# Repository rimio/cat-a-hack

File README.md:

# cat-a-hack

Prototyping board for PC/μC to ham radio transceiver isolation.

 This work is licensed under a [Creative Commons Attribution-ShareAlike 4.0 International License](http://creativecommons.org/licenses/by-sa/4.0/).

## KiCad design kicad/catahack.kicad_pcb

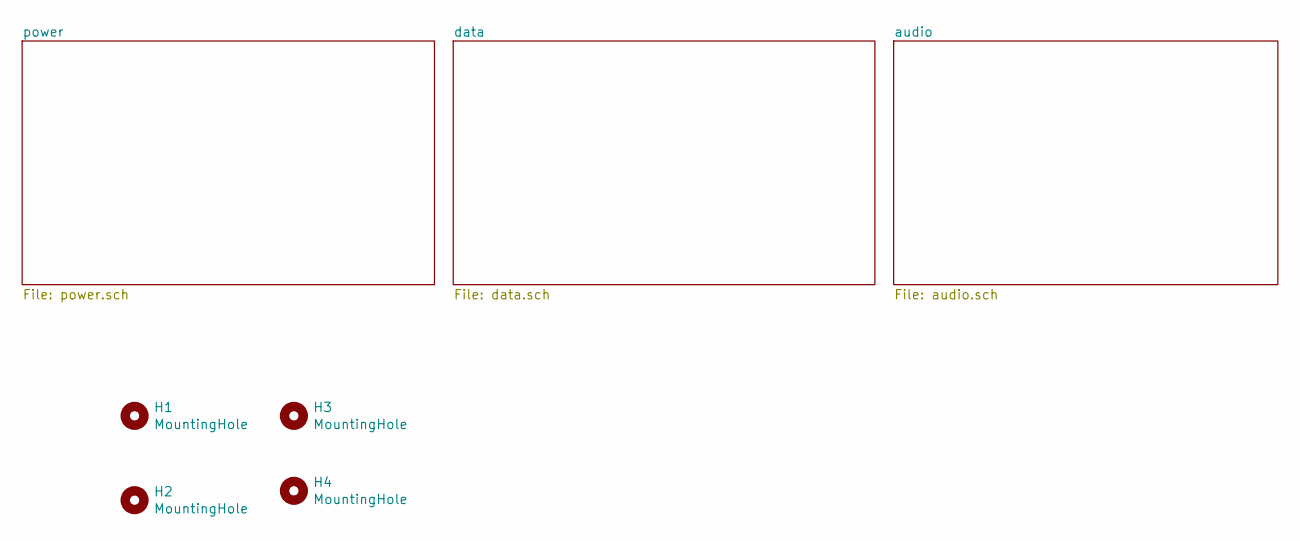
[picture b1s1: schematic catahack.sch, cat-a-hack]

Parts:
H1, H2, H3, H4: MountingHole; MountingHole_4.3mm_M4_ISO7380_Pad

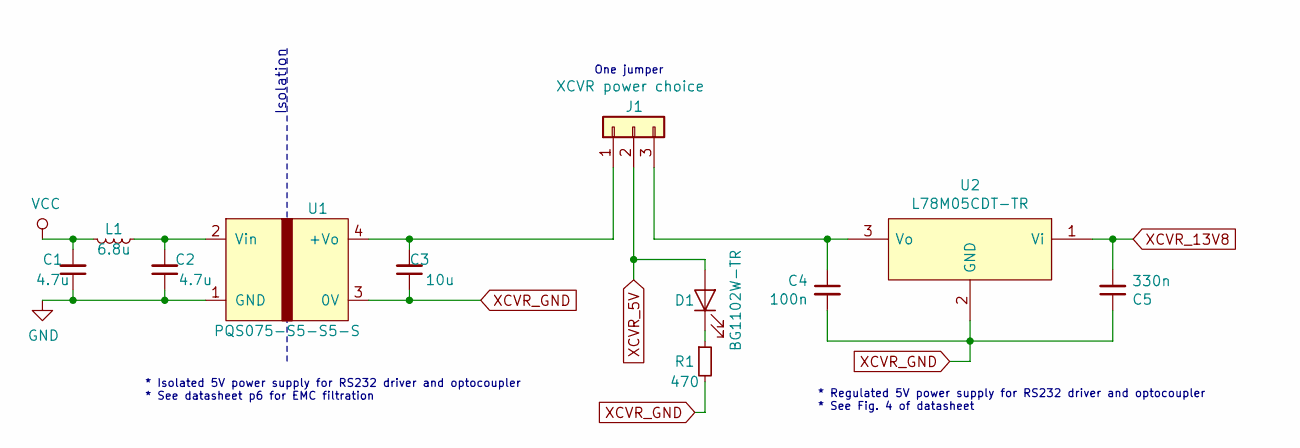
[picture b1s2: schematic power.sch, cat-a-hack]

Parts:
C1, C2: 4.7u; C_1206_3216Metric_Pad1.42x1.75mm_HandSolder
C3: 10u; C_1206_3216Metric_Pad1.42x1.75mm_HandSolder
C4: 100n; C_1206_3216Metric_Pad1.42x1.75mm_HandSolder
C5: 330n; C_1206_3216Metric_Pad1.42x1.75mm_HandSolder
D1: BG1102W-TR; LED_1206_3216Metric_Pad1.42x1.75mm_HandSolder
J1: XCVR power choice; PinHeader_1x03_P2.54mm_Vertical
L1: 6.8u; L_0805_2012Metric_Pad1.15x1.40mm_HandSolder
R1: 470; R_1206_3216Metric_Pad1.42x1.75mm_HandSolder
U1: PQS075-S5-S5-S; SIP-4_PQS075-S5-S5-S
U2: L78M05CDT-TR; TO-252-2; Mouser Part Number 511-L78M05CDT-TR

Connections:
GND: C1.1, C2.1, U1.1 (GND); also elsewhere on the board
unnamed: C2.2, L1.1, U1.2 (Vin)
unnamed: C3.2, J1.1, U1.4 (+Vo)
unnamed: C4.1, J1.3, U2.3 (Vo)
unnamed: D1.1 (K), R1.1
VCC: C1.2, L1.2; also elsewhere on the board
XCVR_5V: D1.2 (A), J1.2; also elsewhere on the board
XCVR_13V8: C5.2, U2.1 (Vi); also elsewhere on the board
XCVR_GND: C3.1, C4.2, C5.1, R1.2, U1.3 (0V), U2.2 (GND); also elsewhere on the board

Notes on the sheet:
* Isolated 5V power supply for RS232 driver and optocoupler * See datasheet p6 for EMC filtration
One jumper
Isolation
* Regulated 5V power supply for RS232 driver and optocoupler * See Fig. 4 of datasheet

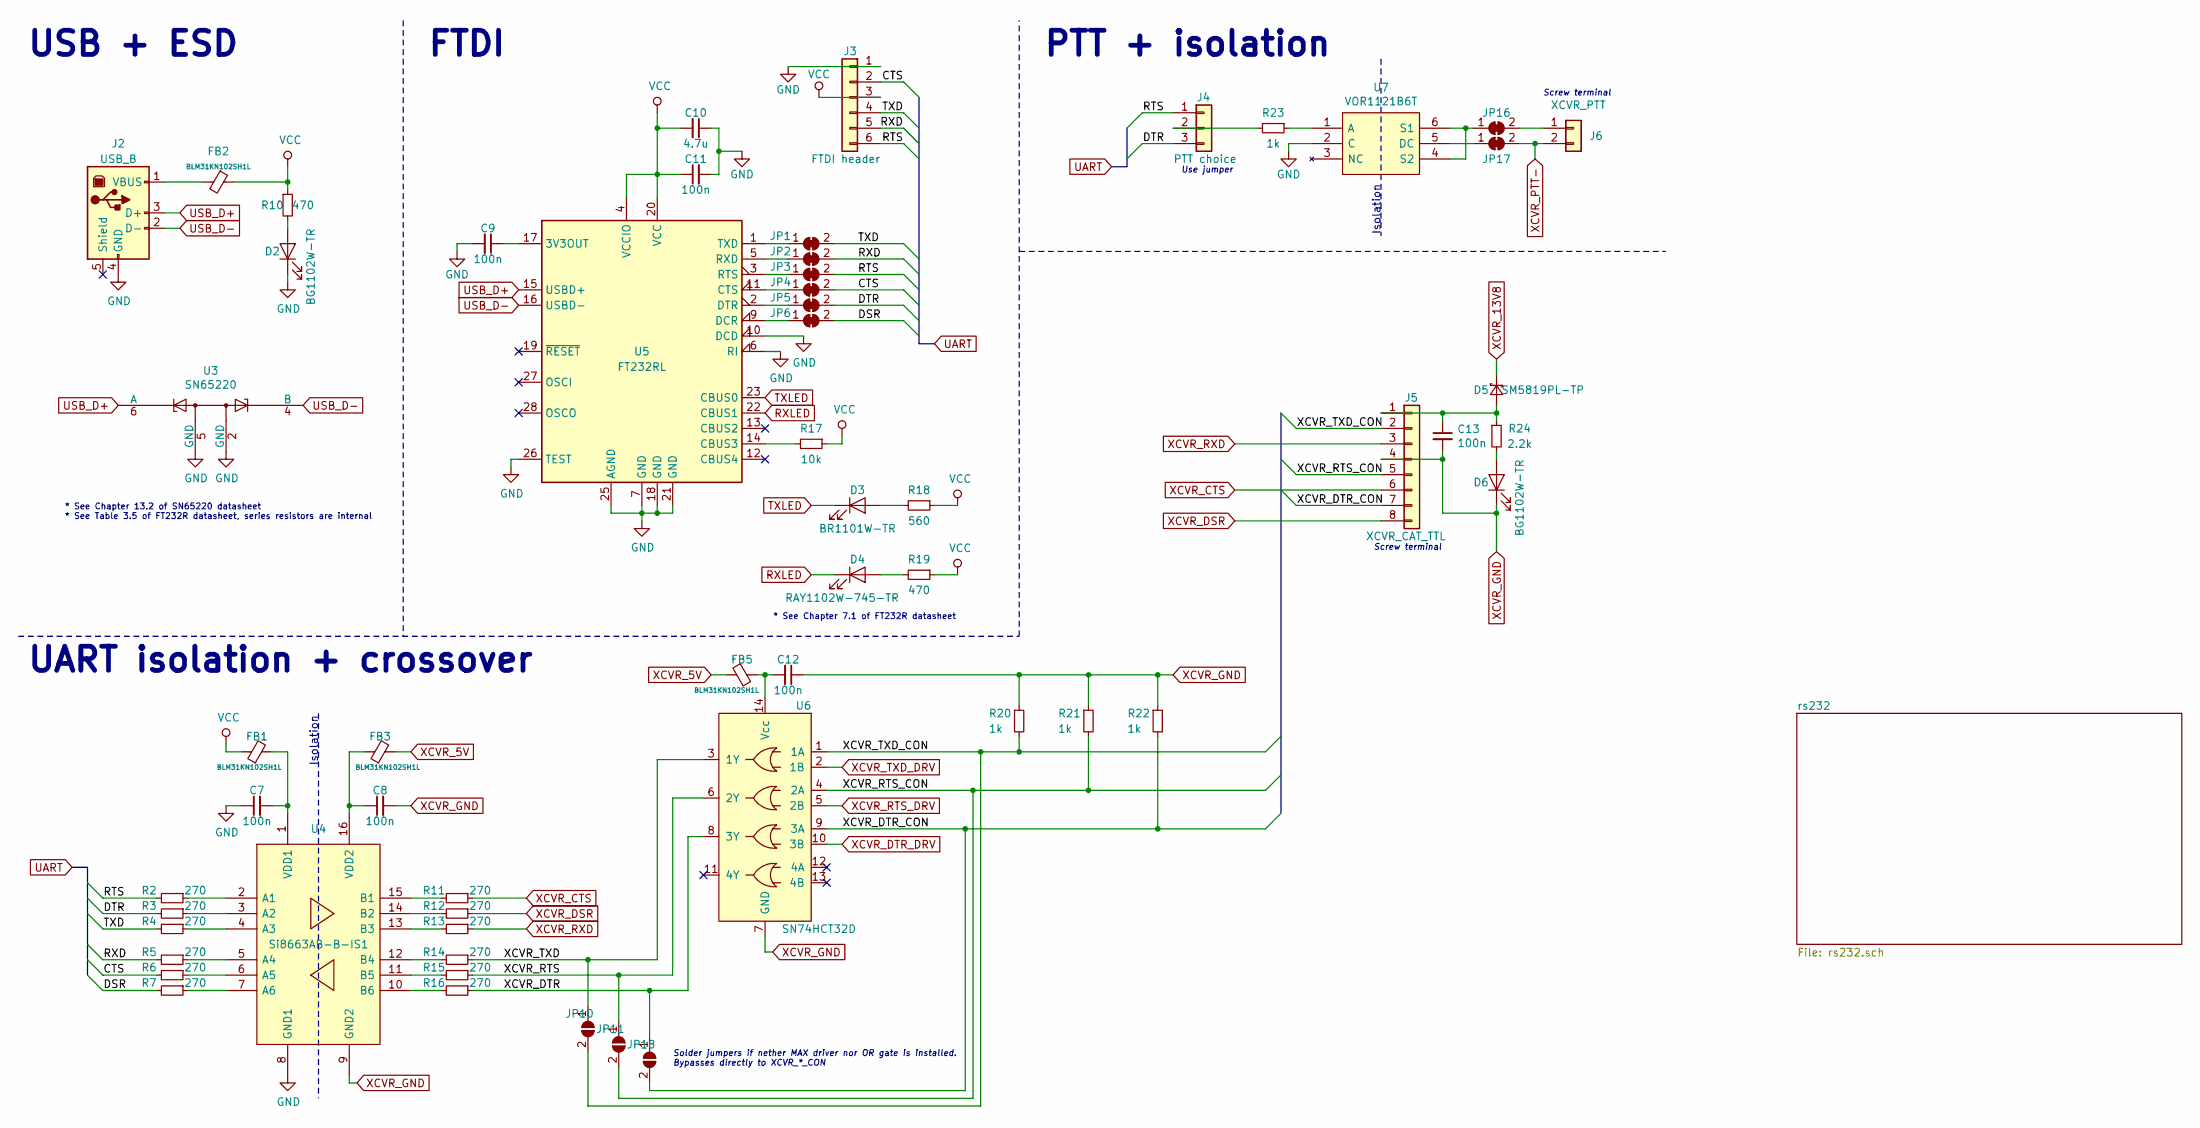
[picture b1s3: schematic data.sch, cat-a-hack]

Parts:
C7, C8, C9, C11, C12, C13: 100n; C_1206_3216Metric_Pad1.42x1.75mm_HandSolder
C10: 4.7u; C_1206_3216Metric_Pad1.42x1.75mm_HandSolder
D2, D6: BG1102W-TR; LED_1206_3216Metric_Pad1.42x1.75mm_HandSolder
D3: BR1101W-TR; LED_1206_3216Metric_Pad1.42x1.75mm_HandSolder
D4: RAY1102W-745-TR; LED_1206_3216Metric_Pad1.42x1.75mm_HandSolder
D5: SM5819PL-TP; D_SOD-123F
FB1, FB2, FB3, FB5: BLM31KN102SH1L; L_1206_3216Metric_Pad1.42x1.75mm_HandSolder
J2: USB_B; USB_B_OST_USB-B1HSxx_Horizontal
J3: FTDI header; PinHeader_1x06_P2.54mm_Vertical
J4: PTT choice; PinHeader_1x03_P2.54mm_Vertical
J5: XCVR_CAT_TTL; TB003-500-P08BE
J6: XCVR_PTT; TB003-500-P02BE
JP1, JP2, JP3, JP4, JP5, JP6, JP16, JP17: SolderJumper_2_Bridged; SolderJumper-2_P1.3mm_Bridged_RoundedPad1.0x1.5mm
JP10, JP11, JP18: SolderJumper_2_Open; SolderJumper-2_P1.3mm_Open_RoundedPad1.0x1.5mm
R2, R3, R4, R5, R6, R7, R11, R12, R13, R14, R15, R16: 270; R_1206_3216Metric_Pad1.42x1.75mm_HandSolder
R10, R19: 470; R_1206_3216Metric_Pad1.42x1.75mm_HandSolder
R17: 10k; R_1206_3216Metric_Pad1.42x1.75mm_HandSolder
R18: 560; R_1206_3216Metric_Pad1.42x1.75mm_HandSolder
R20, R21, R22, R23: 1k; R_1206_3216Metric_Pad1.42x1.75mm_HandSolder
R24: 2.2k; R_1206_3216Metric_Pad1.42x1.75mm_HandSolder
U3: SN65220; SOT-23-6_Handsoldering
U4: Si8663AB-B-IS1; SOIC-16_3.9x9.9mm_P1.27mm; Mouser Part Number 634-SI8663AB-B-IS1
U5: FT232RL; SSOP-28_5.3x10.2mm_P0.65mm
U6: SN74HCT32D; SOIC-14_P1.27mm_Handsolder
U7: VOR1121B6T; SMDIP-6_W9.53mm_Clearance8mm; Mouser Part Number 78-VOR1121B6T

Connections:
/data/CTS: J3.2, JP4.2 (B), R6.2
/data/DSR: JP6.2 (B), R7.2
/data/DTR: J4.3, JP5.2 (B), R3.2
/data/RTS: J3.6, J4.1, JP3.2 (B), R2.2
/data/RXD: J3.5, JP2.2 (B), R5.2
/data/TXD: J3.4, JP1.2 (B), R4.2
/data/XCVR_DTR: JP18.1 (A), R16.1, U6.8 (3Y)
/data/XCVR_DTR_CON: J5.7, JP18.2 (B), R22.2, U6.9 (3A)
/data/XCVR_RTS: JP11.1 (A), R15.1, U6.6 (2Y)
/data/XCVR_RTS_CON: J5.5, JP11.2 (B), R21.2, U6.4 (2A)
/data/XCVR_TXD: JP10.1 (A), R14.1, U6.3 (1Y)
/data/XCVR_TXD_CON: J5.2, JP10.2 (B), R20.2, U6.1 (1A)
GND: C7.1, C9.2, C10.1, C11.2, D2.1 (K), J2.4 (GND), J3.1, U3.2 (GND), U3.5 (GND), U4.8 (GND1), U5.6 (RI), U5.7 (GND), U5.10 (DCD), U5.18 (GND), U5.21 (GND), U5.25 (AGND), U5.26 (TEST), U7.2 (C); also elsewhere on the board
unnamed: C7.2, FB1.2, U4.1 (VDD1)
unnamed: C8.1, FB3.1, U4.16 (VDD2)
unnamed: C9.1, U5.17 (3V3OUT)
unnamed: C12.2, FB5.2, U6.14 (Vcc)
unnamed: C13.1, D5.2 (A), J5.1, R24.1
unnamed: D2.2 (A), R10.2
unnamed: D3.2 (A), R18.2
unnamed: D4.2 (A), R19.2
unnamed: D6.2 (A), R24.2
unnamed: FB2.2, J2.1 (VBUS)
unnamed: J4.2, R23.2
unnamed: J6.1, JP16.2 (B)
unnamed: JP1.1 (A), U5.1 (TXD)
unnamed: JP2.1 (A), U5.5 (RXD)
unnamed: JP3.1 (A), U5.3 (RTS)
unnamed: JP4.1 (A), U5.11 (CTS)
unnamed: JP5.1 (A), U5.2 (DTR)
unnamed: JP6.1 (A), U5.9 (DCR)
unnamed: JP16.1 (A), U7.4 (S2), U7.6 (S1)
unnamed: JP17.1 (A), U7.5 (DC)
unnamed: R2.1, U4.2 (A1)
unnamed: R3.1, U4.3 (A2)
unnamed: R4.1, U4.4 (A3)
unnamed: R5.1, U4.5 (A4)
unnamed: R6.1, U4.6 (A5)
unnamed: R7.1, U4.7 (A6)
unnamed: R11.2, U4.15 (B1)
unnamed: R12.2, U4.14 (B2)
unnamed: R13.2, U4.13 (B3)
unnamed: R14.2, U4.12 (B4)
unnamed: R15.2, U4.11 (B5)
unnamed: R16.2, U4.10 (B6)
unnamed: R17.2, U5.14 (CBUS3)
unnamed: R23.1, U7.1 (A)
RXLED: D4.1 (K), U5.22 (CBUS1)
TXLED: D3.1 (K), U5.23 (CBUS0)
USB_D+: J2.3 (D+), U3.6 (A), U5.15 (USBD+)
USB_D-: J2.2 (D-), U3.4 (B), U5.16 (USBD-)
VCC: C10.2, C11.1, FB1.1, FB2.1, J3.3, R10.1, R17.1, R18.1, R19.1, U5.4 (VCCIO), U5.20 (VCC); also elsewhere on the board
XCVR_5V: FB3.2, FB5.1; also elsewhere on the board
XCVR_13V8: D5.1 (K); also elsewhere on the board
XCVR_CTS: J5.6, R11.1; also elsewhere on the board
XCVR_DSR: J5.8, R12.1; also elsewhere on the board
XCVR_DTR_DRV: U6.10 (3B); also elsewhere on the board
XCVR_GND: C8.2, C12.1, C13.2, D6.1 (K), J5.4, R20.1, R21.1, R22.1, U4.9 (GND2), U6.7 (GND); also elsewhere on the board
XCVR_PTT-: J6.2, JP17.2 (B); also elsewhere on the board
XCVR_RTS_DRV: U6.5 (2B); also elsewhere on the board
XCVR_RXD: J5.3, R13.1; also elsewhere on the board
XCVR_TXD_DRV: U6.2 (1B); also elsewhere on the board

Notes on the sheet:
* See Chapter 13.2 of SN65220 datasheet * See Table 3.5 of FT232R datasheet, series resistors are internal
* See Chapter 7.1 of FT232R datasheet
USB + ESD
FTDI
PTT + isolation
Use jumper
Screw terminal
UART isolation + crossover
Isolation
Solder jumpers if nether MAX driver nor OR gate is installed. Bypasses directly to XCVR_*_CON

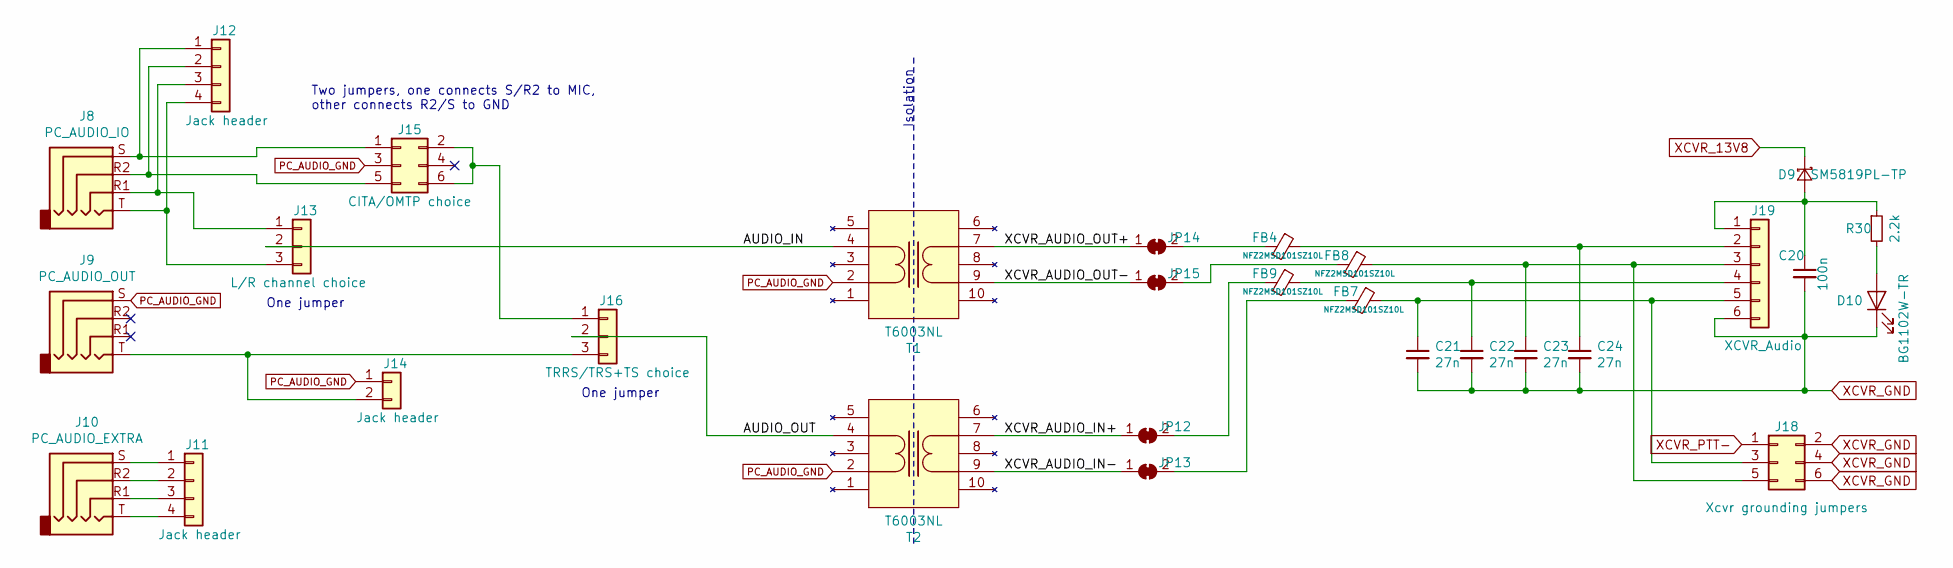
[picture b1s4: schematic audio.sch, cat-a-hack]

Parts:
C20: 100n; C_1206_3216Metric_Pad1.42x1.75mm_HandSolder
C21, C22, C23, C24: 27n; C_1206_3216Metric_Pad1.42x1.75mm_HandSolder
D9: SM5819PL-TP; D_SOD-123F
D10: BG1102W-TR; LED_1206_3216Metric_Pad1.42x1.75mm_HandSolder
FB4, FB7, FB8, FB9: NFZ2MSD101SZ10L; NFZ2MSD101SZ10L_0806_Handsolder
J8: PC_AUDIO_IO; SJ43514
J9: PC_AUDIO_OUT; SJ43514
J10: PC_AUDIO_EXTRA; SJ43514
J11, J12: Jack header; PinHeader_1x04_P2.54mm_Vertical
J13: L/R channel choice; PinHeader_1x03_P2.54mm_Vertical
J14: Jack header; PinHeader_1x02_P2.54mm_Vertical
J15: CITA/OMTP choice; PinHeader_2x03_P2.54mm_Vertical
J16: TRRS/TRS+TS choice; PinHeader_1x03_P2.54mm_Vertical
J18: Xcvr grounding jumpers; PinHeader_2x03_P2.54mm_Vertical
J19: XCVR_Audio; TB003-500-P06BE
JP12, JP13, JP14, JP15: SolderJumper_2_Bridged; SolderJumper-2_P1.3mm_Bridged_RoundedPad1.0x1.5mm
R30: 2.2k; R_1206_3216Metric_Pad1.42x1.75mm_HandSolder
T1, T2: T6003NL; T6003NL_HandSolder; Mouser Part Number 673-T6003NL

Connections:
/audio/AUDIO_IN: J13.2, T1.4
/audio/AUDIO_OUT: J16.2, T2.4
/audio/XCVR_AUDIO_IN+: JP12.1 (A), T2.7
/audio/XCVR_AUDIO_IN-: JP13.1 (A), T2.9
/audio/XCVR_AUDIO_OUT+: JP14.1 (A), T1.7
/audio/XCVR_AUDIO_OUT-: JP15.1 (A), T1.9
unnamed: C20.1, D9.2 (A), J19.1, R30.1
unnamed: C21.1, FB7.1, J18.3, J19.5
unnamed: C22.1, FB9.1, J19.4
unnamed: C23.1, FB8.1, J18.5, J19.3
unnamed: C24.1, FB4.1, J19.2
unnamed: D10.2 (A), R30.2
unnamed: FB4.2, JP14.2 (B)
unnamed: FB7.2, JP13.2 (B)
unnamed: FB8.2, JP15.2 (B)
unnamed: FB9.2, JP12.2 (B)
unnamed: J10.R1, J11.3
unnamed: J10.R2, J11.2
unnamed: J10.S, J11.1
unnamed: J10.T, J11.4
unnamed: J8.S, J12.1, J15.1
unnamed: J8.R2, J12.2, J15.5
unnamed: J8.R1, J12.3, J13.1
unnamed: J8.T, J12.4, J13.3
unnamed: J9.T, J14.2, J16.3
unnamed: J15.2, J15.6, J16.1
PC_AUDIO_GND: J9.S, J14.1, J15.3, T1.2, T2.2
XCVR_13V8: D9.1 (K); also elsewhere on the board
XCVR_GND: C20.2, C21.2, C22.2, C23.2, C24.2, D10.1 (K), J18.2, J18.4, J18.6, J19.6; also elsewhere on the board
XCVR_PTT-: J18.1; also elsewhere on the board

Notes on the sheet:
Isolation
Two jumpers, one connects S/R2 to MIC, other connects R2/S to GND
One jumper

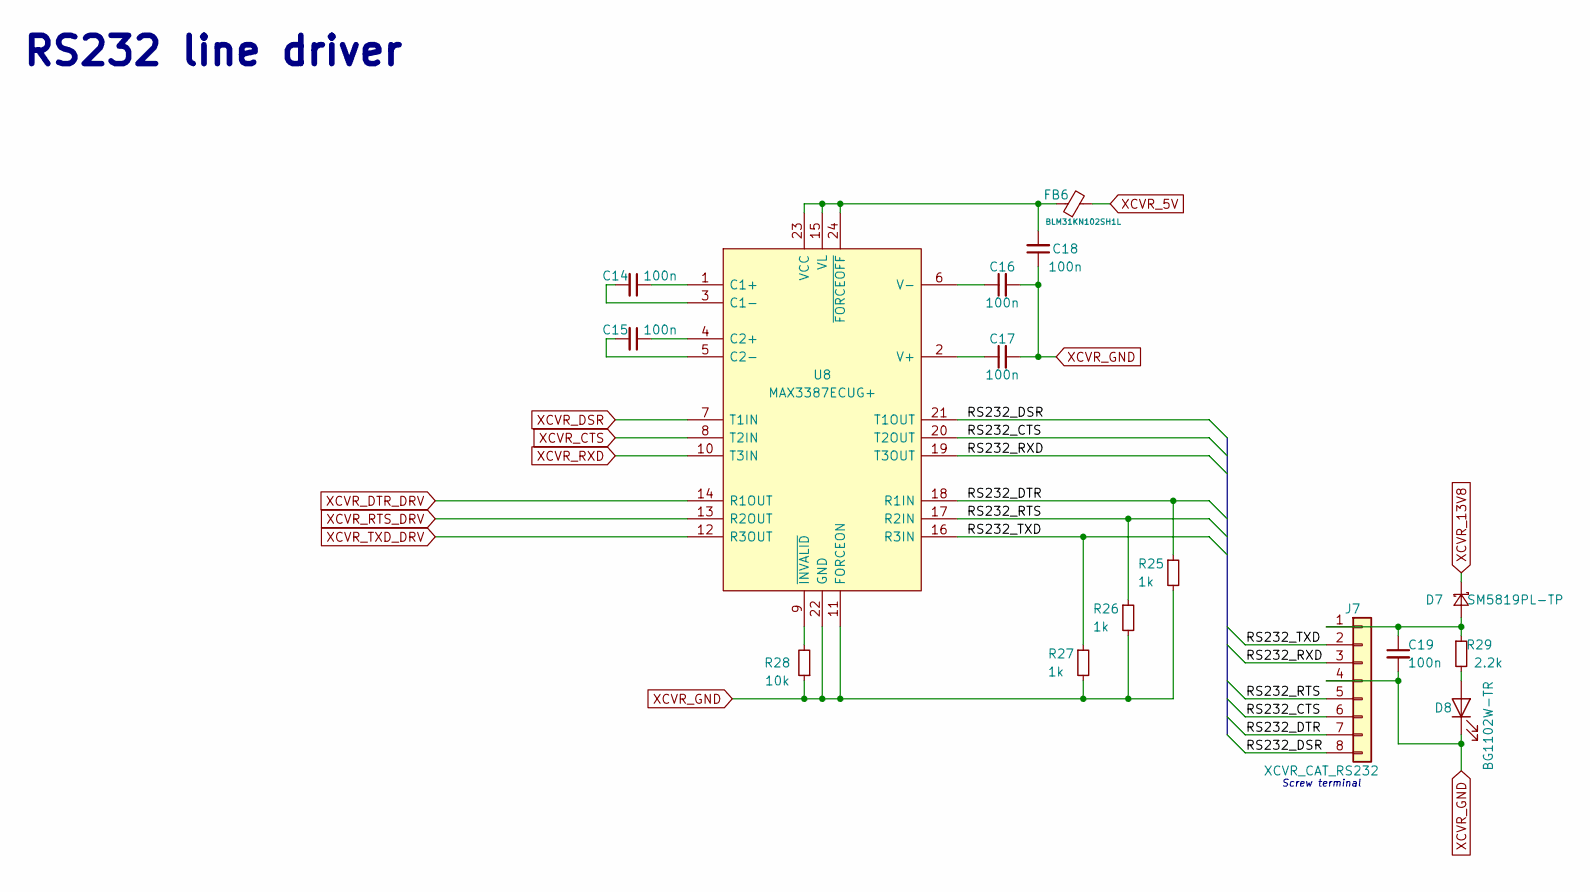
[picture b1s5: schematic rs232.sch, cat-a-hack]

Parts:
C14, C15, C16, C17, C18, C19: 100n; C_1206_3216Metric_Pad1.42x1.75mm_HandSolder
D7: SM5819PL-TP; D_SOD-123F
D8: BG1102W-TR; LED_1206_3216Metric_Pad1.42x1.75mm_HandSolder
FB6: BLM31KN102SH1L; L_1206_3216Metric_Pad1.42x1.75mm_HandSolder
J7: XCVR_CAT_RS232; TB003-500-P08BE
R25, R26, R27: 1k; R_1206_3216Metric_Pad1.42x1.75mm_HandSolder
R28: 10k; R_1206_3216Metric_Pad1.42x1.75mm_HandSolder
R29: 2.2k; R_1206_3216Metric_Pad1.42x1.75mm_HandSolder
U8: MAX3387ECUG+; TSSOP-24_4.4x7.8mm_P0.65mm; Mouser Part Number 700-MAX3387ECUG

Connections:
/data/rs232/RS232_CTS: J7.6, U8.20 (T2OUT)
/data/rs232/RS232_DSR: J7.8, U8.21 (T1OUT)
/data/rs232/RS232_DTR: J7.7, R25.1, U8.18 (R1IN)
/data/rs232/RS232_RTS: J7.5, R26.1, U8.17 (R2IN)
/data/rs232/RS232_RXD: J7.3, U8.19 (T3OUT)
/data/rs232/RS232_TXD: J7.2, R27.1, U8.16 (R3IN)
unnamed: C14.1, U8.1 (C1+)
unnamed: C14.2, U8.3 (C1-)
unnamed: C15.1, U8.4 (C2+)
unnamed: C15.2, U8.5 (C2-)
unnamed: C16.1, U8.6 (V-)
unnamed: C17.1, U8.2 (V+)
unnamed: C18.2, FB6.1, U8.15 (VL), U8.23 (VCC), U8.24 (~FORCEOFF)
unnamed: C19.1, D7.2 (A), J7.1, R29.1
unnamed: D8.2 (A), R29.2
unnamed: R28.2, U8.9 (~INVALID)
XCVR_5V: FB6.2; also elsewhere on the board
XCVR_13V8: D7.1 (K); also elsewhere on the board
XCVR_CTS: U8.8 (T2IN); also elsewhere on the board
XCVR_DSR: U8.7 (T1IN); also elsewhere on the board
XCVR_DTR_DRV: U8.14 (R1OUT); also elsewhere on the board
XCVR_GND: C16.2, C17.2, C18.1, C19.2, D8.1 (K), J7.4, R25.2, R26.2, R27.2, R28.1, U8.11 (FORCEON), U8.22 (GND); also elsewhere on the board
XCVR_RTS_DRV: U8.13 (R2OUT); also elsewhere on the board
XCVR_RXD: U8.10 (T3IN); also elsewhere on the board
XCVR_TXD_DRV: U8.12 (R3OUT); also elsewhere on the board

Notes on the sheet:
RS232 line driver
Screw terminal

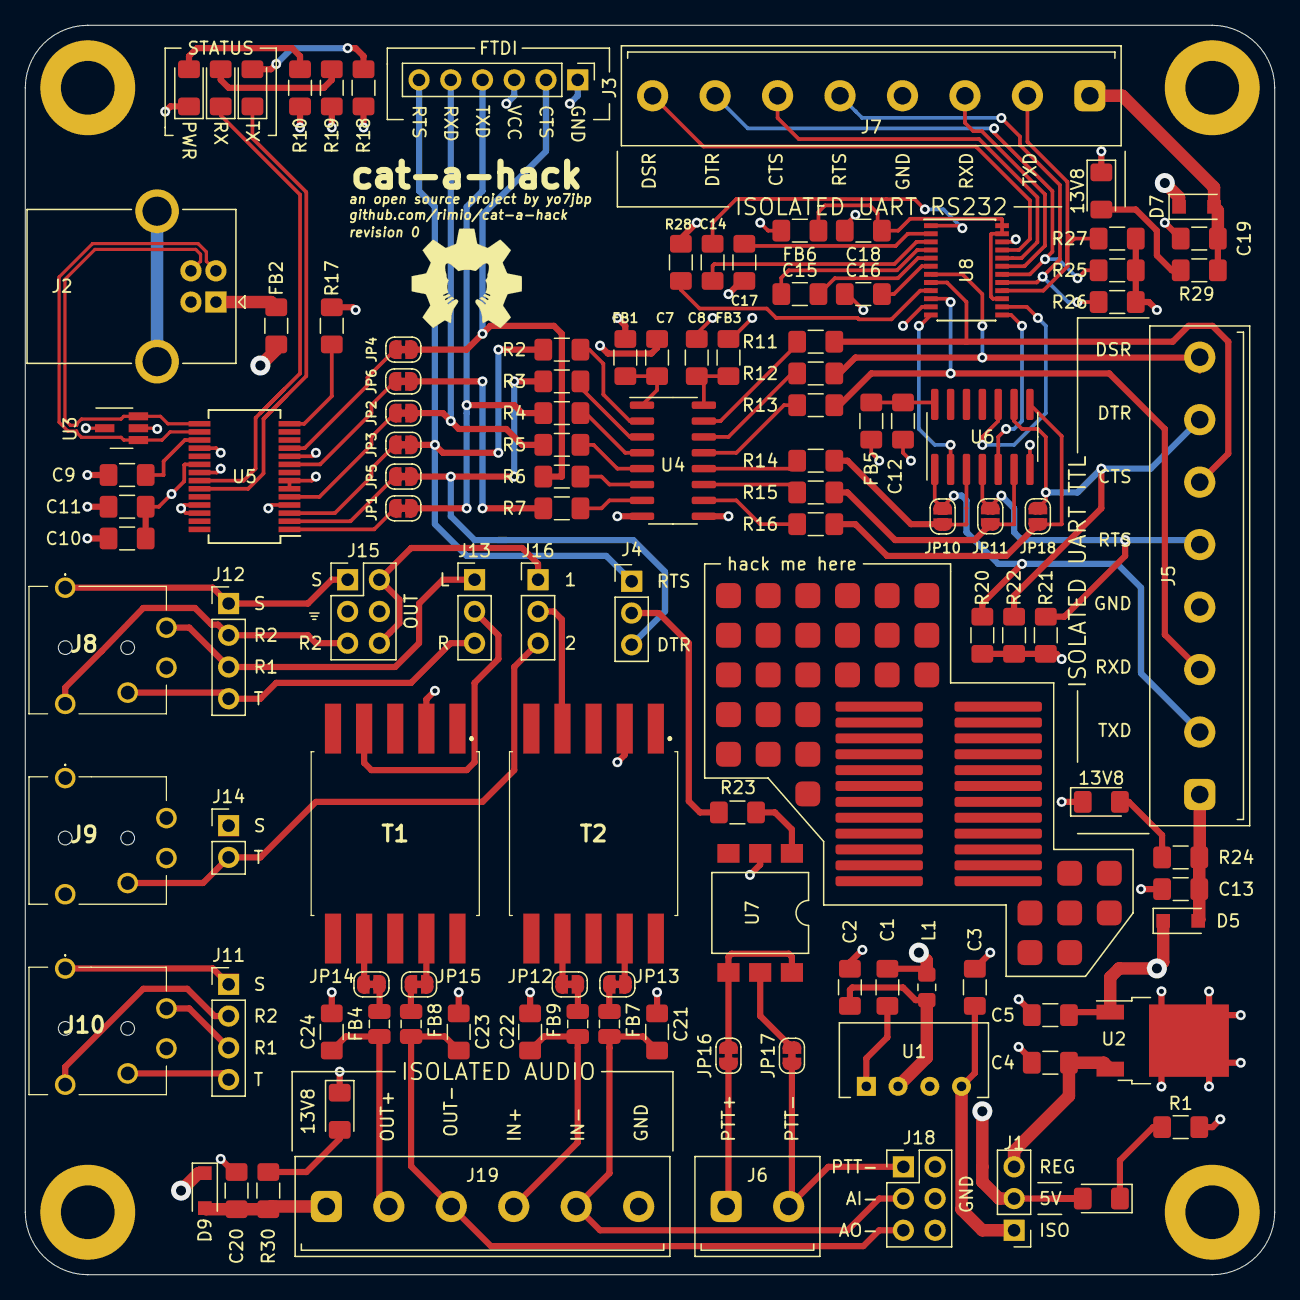
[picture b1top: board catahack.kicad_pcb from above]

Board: 4 copper layers, 100.0 x 100.0 mm, 118 parts (0 on the bottom side), 109 nets.

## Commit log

2020-10-31 Add kicad dir
2020-10-31 Initial commit.
2020-10-31 Change DC-DC convertor; other small changes
    * Change RFM-0505S (unregulated) to PQS075-S5-S5-S (regulated)
    * Naming conventions
    * Alignment
2020-10-31 Fixed reversed I/O on MAX line driver
2020-11-01 Filtering, jumpers, LEDs, misc
    * Modified high level diagram to express the shared UART bus
    * Renamed XCVR_VCC to XCVR_13V8
    * Add solder jumpers on audio, PTT and UART lines for easy prototyping/bypassing
    * Added bypass caps on XCVR side data and audio connectors
    * Add series ferite beads on data ICs Vcc
    * Added schottky diodes to all XCVR_13V8
2020-11-01 MAX driver protection
    * Adjust label position for readability
    * Protected R1OUT-R3OUT of MAX driver with OR gate
2020-11-01 Connector and pull down resistors
    * Changed back to USB-B connector.
    * Changed value of pull down resistors to 1k.
2020-11-02 Initial footprint placement + changes
    * Added initial placement
    * Remove pull-down resistors from USB lines.
    * Remove ferrite bead from FTDI chip as it was very close to Vcc FB
    * Fixed MAX TX pins
    * Assigned footprints.
    * Removed redundant solder jumpers.
2020-11-03 New layout, routing, misc...
    * Redo layout
    * Fixed MAX pulldown resistors on data lines.
    * Added jumpers in case MAX not installed.
    * Remove audio header
    * Remove some redundant solder jumpers
2020-11-03 Logo and small corrections
    * Added logo
    * Connected a few unconnected pads
    * Fixed GND pour intersection
2020-11-04 Audio filtering, hackable area, misc
    * Added bypass caps and ferrites to audio lines
    * Small rerouting
    * Hackable area
    * Added rev no
2020-11-04 Ferrite beads, hacking pads, audio fix
    * Chose ferrite beads for IC Vcc (BLM31KN102SH1L)
    * Change hacking pad thickness to 0.8mm
    * Fixed potential oscillator when grounding audio- lines
2020-11-05 Removed extra bypass cap from USB VBUS pin due to closeness to FTDI bypass cap; rerouted some traces
2020-11-05 Small fixes
    * Moved via that was unreasonably close to another one
    * Changed 13V8 diodes to SM5819PL-TP
2020-11-05 Bugfixes
    * Fixed USB D+/D- switch
    * Added clearance at top right mounting hole
2020-11-05 Changed L1 to 0805 due to stock issues
2020-11-07 Changed resistor reference location and size; changed gitignore to include gerber dir
2020-11-09 Enable B soldermask layer; add BOM
2020-11-23 Added rev 0 schematic and gerber files
2021-01-05 Match revision to directory name
2021-01-05 Using board revision
